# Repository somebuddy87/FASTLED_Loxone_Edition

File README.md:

# LOXpixel!  FASTLED Implementierung für Loxone

eine FASTLED Implementierung in Verbindung mit einem ESP8266 Board (NodeMCU)

Einige Zusatzinformationen können in unserem Bau und Smart-Home Blog nachgelesen werden:

https://unser-smartes-zuhause.de/2019/10/20/loxpixel-rgbw-neopixel-integration-in-loxone/

Ich habe mit der Entwicklung im Rahmen meiner Smart-Home Planung für unseren Neubau begonnen. Die Idee war Neopixel ähnliche LED Streifen mit meinem Loxone Miniserver zu verbinden. Und das alles möglichst einfach bedienbar.
# Vor dem Kompilieren zu beachten!!!!!!

 - LED Chip Type und Datenpin lassen sich aktuell noch nicht über das Webinterface einstellen! Hierfür sind Anpassungen im Code notwendig
 - Sofern der DMA Modus (#define FASTLED_ESP8266_DMA) verwendet wird, wird automatisch immer der **RX Pin** des Boards verwendet. Im Falle des NodeMCU ist das Pin3. Der Pin lässt sich im DMA Modus **nicht** anpassen!
 - Maximalen Versionsstand der ESP8266 Plattform beachten ! 
 **( Arduino Versionsnummer 2.5.0 / PlattformIO Versionsnummer 2.0.4 )** 
 
**Arduino:**

**PlattformIO:**

 - Wenn nicht mein Fork der FastLED Bibliothek verwendet wird, muss eine Zeile in folgender Datei auskommentiert werden:
 
 **Arduino:**
 **C:\USERS\Username\Documents\Arduino\libraries\FastLED-master\platforms\esp\8266\led_sysdefs_esp8266.h**
 
     typedef uint8_t boolean;
    zu
    //typedef uint8_t boolean;

## Erster Start
LOXpixel! erstellt bei dem ersten Start einen WLAN Accesspoint mit folgenden Daten:

**SSID: loxpixel!
Passwort: loxpixel**

Nach der Verbindung mit dem Accesspoint, wird man auf die Statusseite verwiesen. Dort müssen zunächst die Grundeinstellungen angepasst werden.

 - Namen (Hostnamen) für die LOXpixel! Platine
 - Feste IP 
 - Subnetzmaske
 - Standardgateway
 - Anzahl der LEDS
 ~~- Datenpin~~
 ~~- LED Controller Typ~~

Der LED Stripe kann in bis zu 8 Abschnitte aufgeteilt werden. Hierbei muss jeweils die erste LED sowie die Länge des Abschnitts angegeben werden.
z.Bsp.:
**Part 1 Anfang :  LED 1
Part 1 Länge:  10
Part 2 Anfang: LED 11**
usw.
## Features
 - Einen neopixel ähnlichen LED Stripe mit bis zu 1200pixel in bis zu 8 Abschnitte aufteilen und einzeln ansteuern (Die Funktion mit mehreren Pixeln und Abschnitten wurde bisher nicht geprüft). 

 - Die Abschnitte des LED Streifen sind aus der Loxone App als einzelne Leuchtmittel ansteuerbar.

- In der Loxone App kann ein Farbverlauf unter Verwendung des kompletten LED Streifen erstellt werden

- Effekte unter Verwendung des kompletten LED Streifen aus der Loxone App starten

Beispielvideo (Testsetup) :

- Einfaches Webinterface zur Einstellung der wichtigsten Parameter

# Software
## Vorraussetzungen
TBD
## VSCode / PlatformIO
TBD
# Hardware
## Verwendete Komponenten
LED Streifen:  [BTF-LIGHTING RGBW RGBNW Natürliches Weiß SK6812 (ähnlich WS2812B) 5m 60leds/pixels/m](https://www.amazon.de/BTF-LIGHTING-Nat%C3%BCrliches-Individuell-adressierbar-nicht-wasserdicht/dp/B01N2PC9KK/ref=as_li_ss_tl?th=1&linkCode=ll1&tag=unsersmarte01-21&linkId=7286a35d1bcb23a684513b37aa95e789&language=de_DE)  *

Netzteil:  [Mean Well LPV-100-5 LED-Trafo Konstantspannung 60W 0-12A 5 V/DC](https://www.amazon.de/gp/product/B00MWQF6M2/ref=as_li_ss_tl?ie=UTF8&psc=1&linkCode=ll1&tag=unsersmarte01-21&linkId=ce2ce103875b0810fd30c44153c2f10d&language=de_DE)  *

## LOXpixel! Prototype Board
TBD
## LOXpixel! V2 Board (Ausblick)
TBD

# Integration in Loxone
TBD

## Vorlage importieren
TBD

Die mit Sternchen (*) gekennzeichneten Links sind sogenannte Affiliate-Links. Wenn du auf so einen Affiliate-Link klickst und über diesen Link einkaufst, bekomme ich von dem betreffenden Online-Shop oder Anbieter eine Provision. Für dich verändert sich der Preis nicht.

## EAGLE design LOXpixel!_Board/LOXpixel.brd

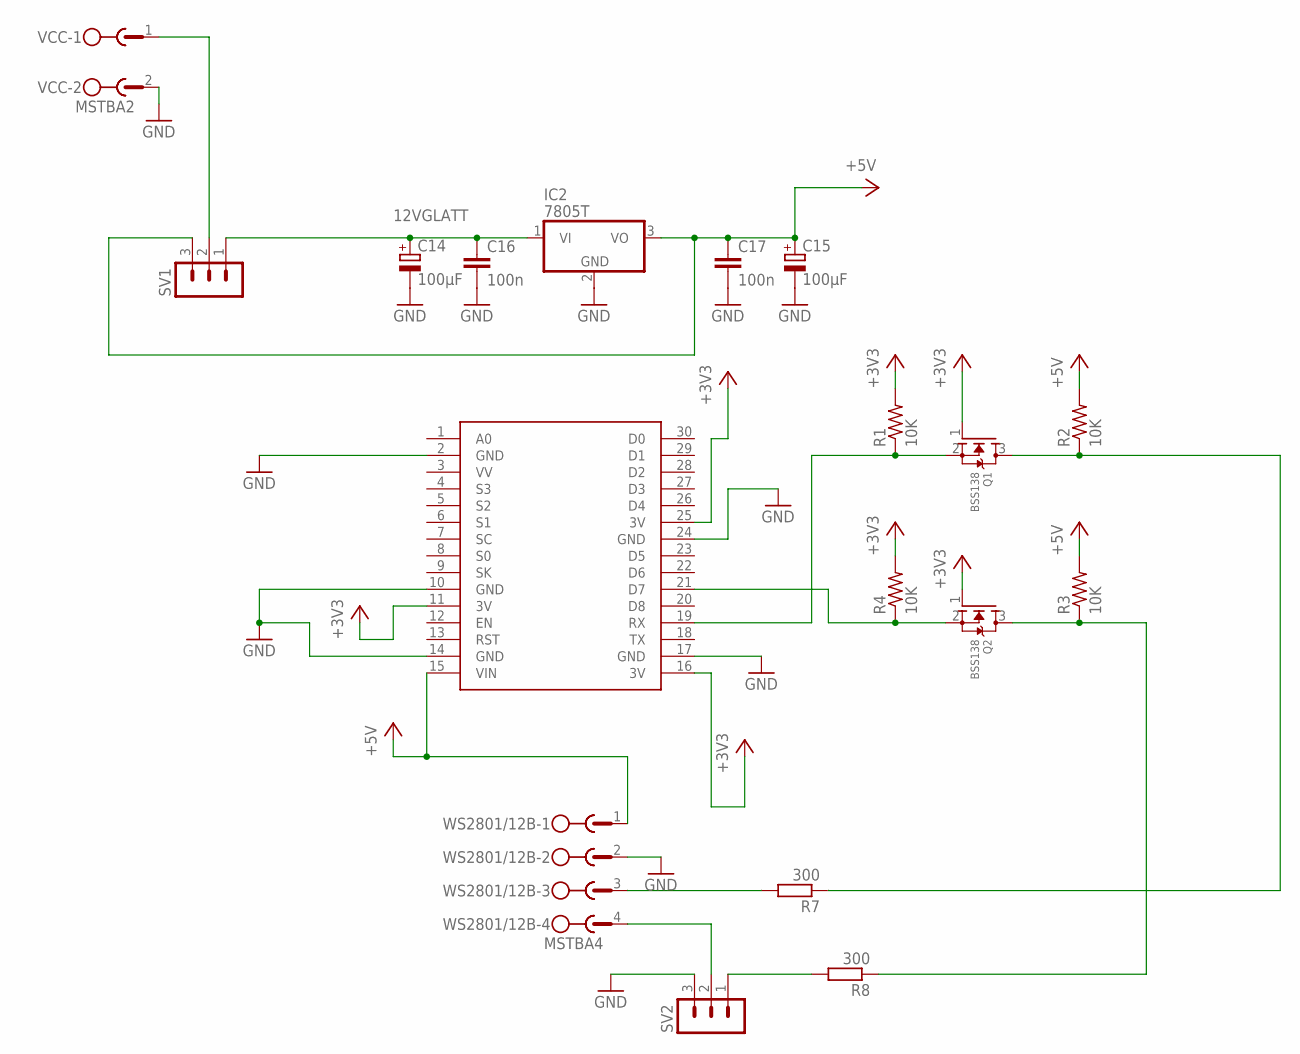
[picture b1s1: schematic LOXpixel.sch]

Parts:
C14, C15: 100µF; 150CLZ-0810
C16, C17: 100n; C0805
IC2: 7805T; TO220H
Q1, Q2: BSS138; SOT23
R1, R2, R3, R4: 10K; R0805
R7, R8: 300; R0805
SV1, SV2: MA03-1
U$1: NODEMCU
VCC: MSTBA2
WS2801/12B: MSTBA4

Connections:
12VGLATT: C14.+, C16.1, IC2.1 (VI), SV1.1
+3V3: Q1.1 (G), Q2.1 (G), R1.2, R4.2, U$1.11 (3V), U$1.16 (3V), U$1.25 (3V)
+5V: C15.+, C17.1, IC2.3 (VO), R2.2, R3.2, SV1.3, U$1.15 (VIN), WS2801/12B.1
GND: C14.-, C15.-, C16.2, C17.2, IC2.2 (GND), SV2.3, U$1.2 (GND), U$1.10 (GND), U$1.14 (GND), U$1.17 (GND), U$1.24 (GND), VCC.2, WS2801/12B.2
unnamed: SV1.2, VCC.1
unnamed: SV2.2, WS2801/12B.4
unnamed: R8.2, SV2.1
unnamed: R7.2, WS2801/12B.3
unnamed: Q1.2 (S), R1.1, U$1.19 (RX)
unnamed: Q1.3 (D), R2.1, R7.1
unnamed: Q2.2 (S), R4.1, U$1.21 (D7)
unnamed: Q2.3 (D), R3.1, R8.1

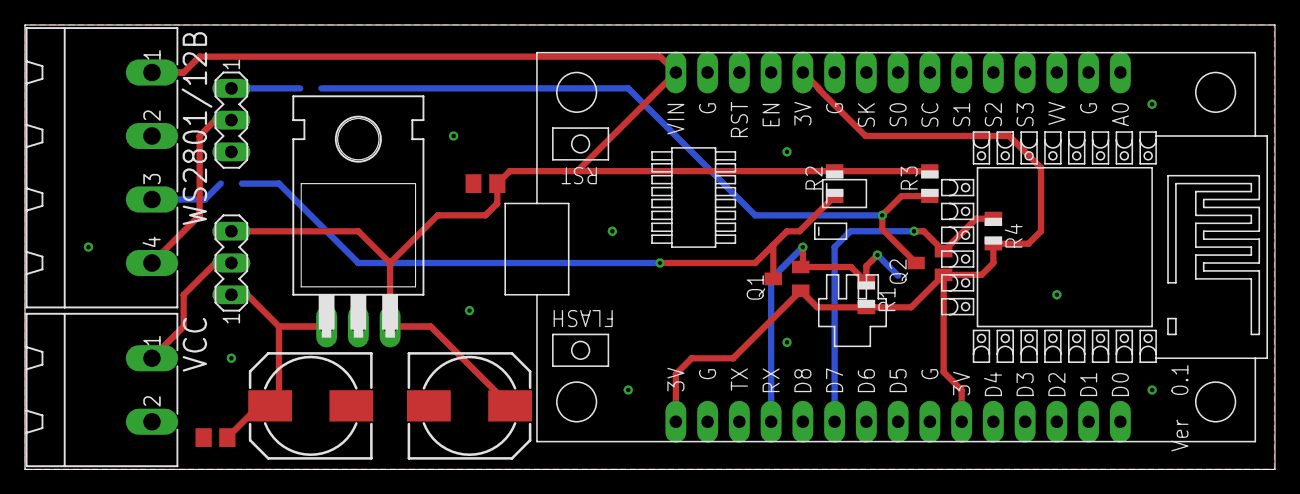
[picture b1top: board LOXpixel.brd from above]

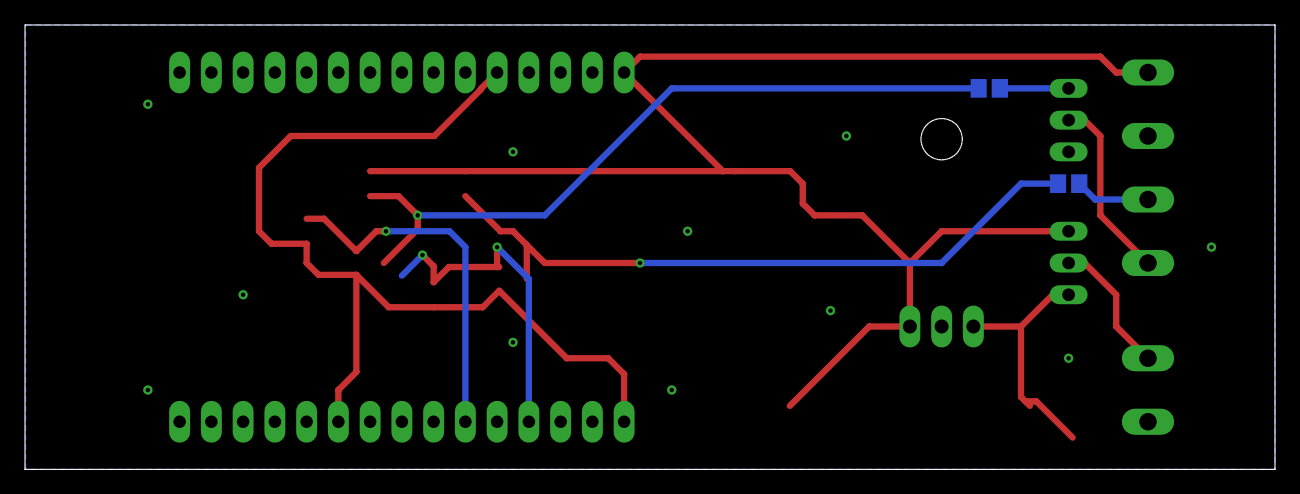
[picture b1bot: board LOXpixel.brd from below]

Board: 2 copper layers, 100.0 x 35.5 mm, 18 parts (2 on the bottom side), 12 nets.

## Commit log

2019-10-20 Upload Board Files
2019-10-22 Update FASTLED_Loxone_Edition.ino
    Switching to DMA and LED_PIN 3. Works fine!
2019-11-02 Commit V0.2
    added some new effect, changed rainbow effect, added webinterface for easy setup, increases LED Stripe Part count to 8
2019-11-02 Add Loxone Virtual Out Template
    Added template for easy LOXpixel! adding into loxone config software
2019-11-02 First Readme
    Added Short Description https://unser-smartes-zuhause.de/2019/10/20/loxpixel-rgbw-neopixel-integration-in-loxone/
2019-11-16 Update main.ino
    - added comment for using RX Pin as LED Pin in DMA mode
    - added Cylon Bounce effect
2019-11-23 fixed initialisation error
    fixed error which prevents LOXpixel from stating
2020-07-13 adaptations for loxpixel board
2020-07-13 WS2811 renamed to WS2812
2020-07-13 some default values added
2022-01-26 Migrate IotWebConf to v3.x.x
    Refactored IotWebConf from v2.3.3 to v3.2.0
    see https://github.com/prampec/IotWebConf/blob/master/doc/MigrationGuide-v3.0.0.md
